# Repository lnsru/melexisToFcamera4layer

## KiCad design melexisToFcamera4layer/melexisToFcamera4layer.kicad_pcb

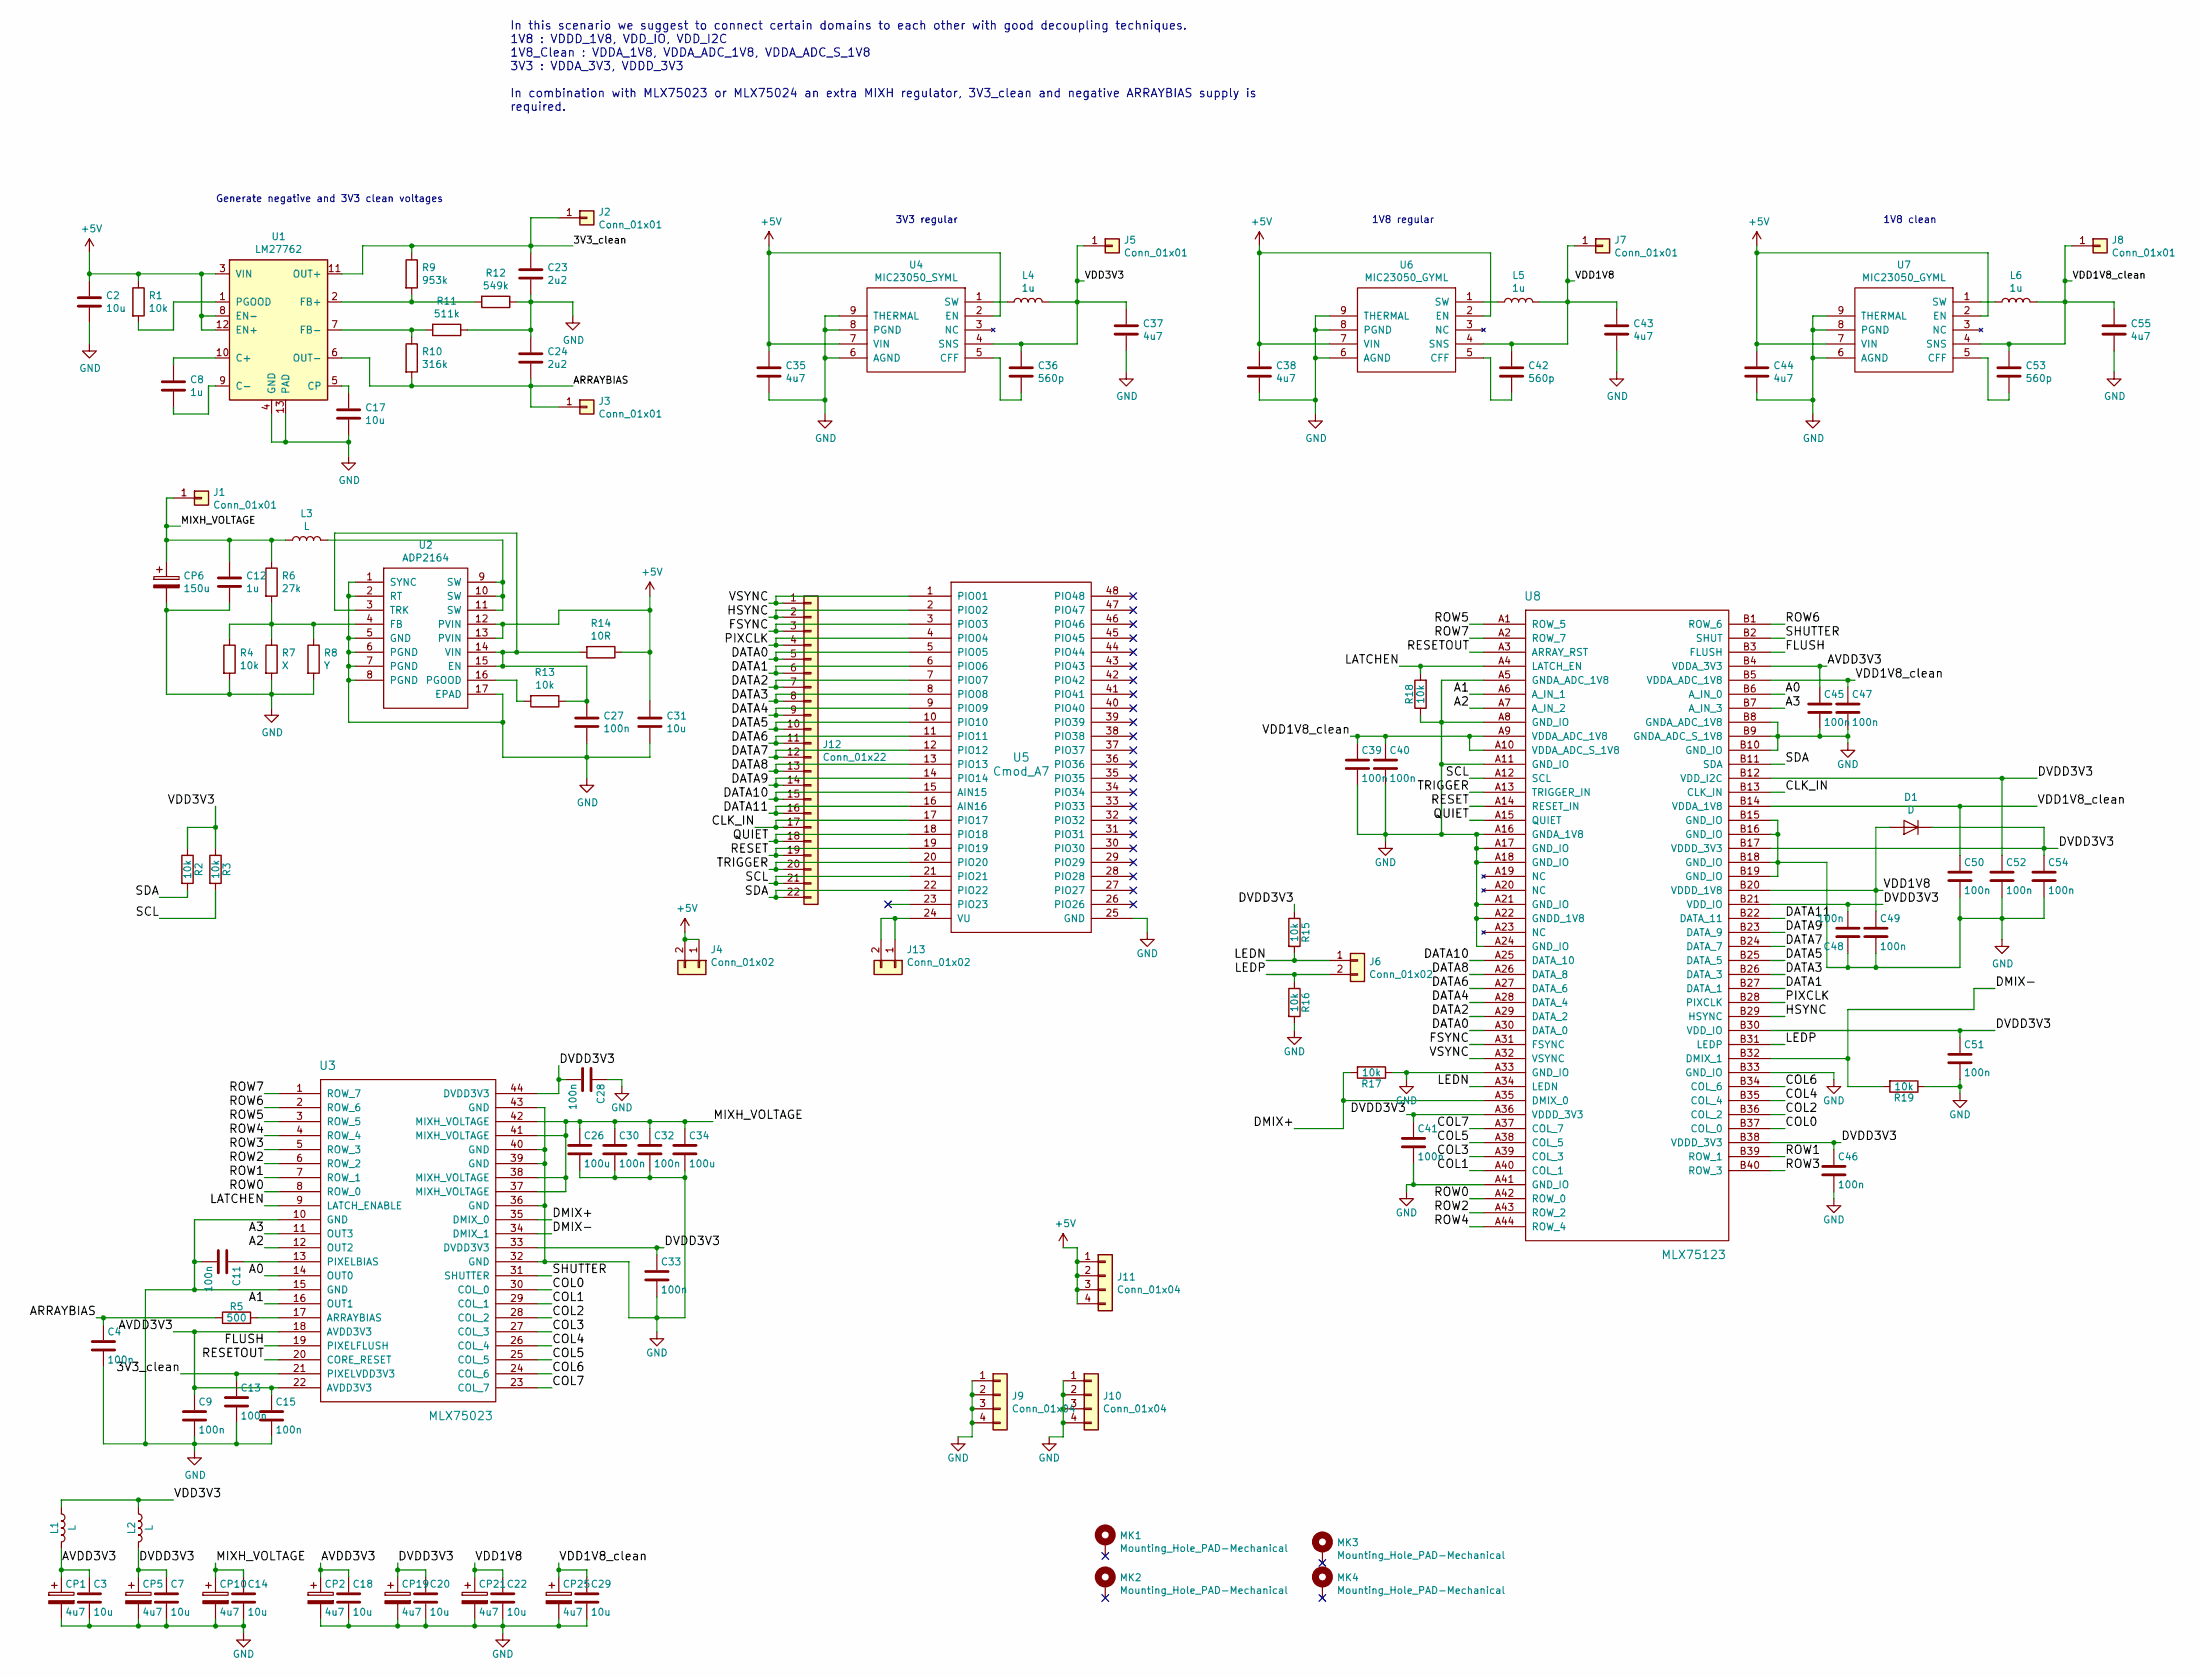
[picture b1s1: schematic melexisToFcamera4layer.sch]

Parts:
C2, C3, C7, C14, C17, C18, C20, C22, C29, C31: 10u; C_0603
C4, C9, C11, C13, C15, C27, C28, C30, C32, C33, C39, C40, C41, C45, C46, C47, C48, C49, C50, C51, C52, C54: 100n; C_0603
C8, C12: 1u; C_0603
C23, C24: 2u2; C_0603
C26, C34: 100u; C_0603
C35, C37, C38, C43, C44, C55: 4u7; C_0603
C36, C42, C53: 560p; C_0603
CP1, CP2, CP5, CP10, CP19, CP21, CP25: 4u7; C_0603
CP6: 150u; C_0603
D1: D; D_0805
J1, J2, J3, J5, J7, J8: Conn_01x01; Measurement_Point_Round-SMD-Pad_Small
J4, J6, J13: Conn_01x02; Pin_Header_Straight_1x02_Pitch2.54mm
J9, J10, J11: Conn_01x04; Pin_Header_Straight_1x04_Pitch2.54mm
J12: Conn_01x22
L1, L2, L3: L; R_1206_HandSoldering
L4, L5, L6: 1u; R_1206_HandSoldering
MK1, MK2, MK3, MK4: Mounting_Hole_PAD-Mechanical; MountingHole_3.2mm_M3_ISO7380
R1, R2, R3, R4, R13, R15, R16, R17, R18, R19: 10k; R_0603
R5: 500; R_0805_HandSoldering
R6: 27k; R_0805_HandSoldering
R7: X; R_0805_HandSoldering
R8: Y; R_0805_HandSoldering
R9: 953k; R_0805_HandSoldering
R10: 316k; R_0805_HandSoldering
R11: 511k; R_0805_HandSoldering
R12: 549k; R_0805_HandSoldering
R14: 10R; R_0805_HandSoldering
U1: LM27762
U2: ADP2164
U3: MLX75023
U4: MIC23050_SYML; MIC23050
U5: Cmod_A7
U6, U7: MIC23050_GYML; MIC23050
U8: MLX75123

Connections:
+5V: C2.1, C31.1, C35.1, C38.1, C44.1, J4.1, J4.2, J11.1, J11.2, J11.3, J11.4, R1.1, R14.1, U1.3 (VIN), U1.8 (EN-), U1.12 (EN+), U2.12 (PVIN), U2.13 (PVIN), U4.2 (EN), U4.7 (VIN), U6.2 (EN), U6.7 (VIN), U7.2 (EN), U7.7 (VIN)
/3V3_clean: C13.1, C23.1, J2.1, R9.1, U1.11 (OUT+), U3.21 (PIXELVDD3V3)
/A0: U3.14 (OUT0), U8.B6 (A_IN_0)
/A1: U3.16 (OUT1), U8.A6 (A_IN_1)
/A2: U3.12 (OUT2), U8.A7 (A_IN_2)
/A3: U3.11 (OUT3), U8.B7 (A_IN_3)
/ARRAYBIAS: C4.1, C24.2, J3.1, R5.1, R10.2, U1.6 (OUT-)
/AVDD3V3: C3.1, C9.1, C15.1, C18.1, C45.1, CP1.1, CP2.1, L1.2, U3.18 (AVDD3V3), U3.22 (AVDD3V3), U8.B4 (VDDA_3V3)
/CLK_IN: J12.17, U5.17 (PIO17), U8.B13 (CLK_IN)
/COL0: U3.30 (COL_0), U8.B37 (COL_0)
/COL1: U3.29 (COL_1), U8.A40 (COL_1)
/COL2: U3.28 (COL_2), U8.B36 (COL_2)
/COL3: U3.27 (COL_3), U8.A39 (COL_3)
/COL4: U3.26 (COL_4), U8.B35 (COL_4)
/COL5: U3.25 (COL_5), U8.A38 (COL_5)
/COL6: U3.24 (COL_6), U8.B34 (COL_6)
/COL7: U3.23 (COL_7), U8.A37 (COL_7)
/DATA0: J12.5, U5.5 (PIO05), U8.A30 (DATA_0)
/DATA1: J12.6, U5.6 (PIO06), U8.B27 (DATA_1)
/DATA2: J12.7, U5.7 (PIO07), U8.A29 (DATA_2)
/DATA3: J12.8, U5.8 (PIO08), U8.B26 (DATA_3)
/DATA4: J12.9, U5.9 (PIO09), U8.A28 (DATA_4)
/DATA5: J12.10, U5.10 (PIO10), U8.B25 (DATA_5)
/DATA6: J12.11, U5.11 (PIO11), U8.A27 (DATA_6)
/DATA7: J12.12, U5.12 (PIO12), U8.B24 (DATA_7)
/DATA8: J12.13, U5.13 (PIO13), U8.A26 (DATA_8)
/DATA9: J12.14, U5.14 (PIO14), U8.B23 (DATA_9)
/DATA10: J12.15, U5.15 (AIN15), U8.A25 (DATA_10)
/DATA11: J12.16, U5.16 (AIN16), U8.B22 (DATA_11)
/DMIX+: R17.2, U3.35 (DMIX_0), U8.A35 (DMIX_0)
/DMIX-: R19.2, U3.34 (DMIX_1), U8.B32 (DMIX_1)
/DVDD3V3: C7.1, C20.1, C28.2, C33.1, C41.1, C46.1, C48.2, C51.1, C52.1, C54.1, CP5.1, CP19.1, D1.1 (K), L2.2, R15.1, U3.33 (DVDD3V3), U3.44 (DVDD3V3), U8.A36 (VDDD_3V3), U8.B12 (VDD_I2C), U8.B17 (VDDD_3V3), U8.B21 (VDD_IO), U8.B30 (VDD_IO), U8.B38 (VDDD_3V3)
/FLUSH: U3.19 (PIXELFLUSH), U8.B3 (FLUSH)
/FSYNC: J12.3, U5.3 (PIO03), U8.A31 (FSYNC)
/HSYNC: J12.2, U5.2 (PIO02), U8.B29 (HSYNC)
/LATCHEN: R18.2, U3.9 (LATCH_ENABLE), U8.A4 (LATCH_EN)
/LEDN: J6.1, R15.2, U8.A34 (LEDN)
/LEDP: J6.2, R16.1, U8.B31 (LEDP)
/MIXH_VOLTAGE: C12.1, C14.1, C26.1, C30.1, C32.1, C34.1, CP6.1, CP10.1, J1.1, L3.1, R6.1, U3.37 (MIXH_VOLTAGE), U3.38 (MIXH_VOLTAGE), U3.41 (MIXH_VOLTAGE), U3.42 (MIXH_VOLTAGE)
/PIXCLK: J12.4, U5.4 (PIO04), U8.B28 (PIXCLK)
/QUIET: J12.18, U5.18 (PIO18), U8.A15 (QUIET)
/RESET: J12.19, U5.19 (PIO19), U8.A14 (RESET_IN)
/RESETOUT: U3.20 (CORE_RESET), U8.A3 (ARRAY_RST)
/ROW0: U3.8 (ROW_0), U8.A42 (ROW_0)
/ROW1: U3.7 (ROW_1), U8.B39 (ROW_1)
/ROW2: U3.6 (ROW_2), U8.A43 (ROW_2)
/ROW3: U3.5 (ROW_3), U8.B40 (ROW_3)
/ROW4: U3.4 (ROW_4), U8.A44 (ROW_4)
/ROW5: U3.3 (ROW_5), U8.A1 (ROW_5)
/ROW6: U3.2 (ROW_6), U8.B1 (ROW_6)
/ROW7: U3.1 (ROW_7), U8.A2 (ROW_7)
/SCL: J12.21, R3.2, U5.21 (PIO21), U8.A12 (SCL)
/SDA: J12.22, R2.2, U5.22 (PIO22), U8.B11 (SDA)
/SHUTTER: U3.31 (SHUTTER), U8.B2 (SHUT)
/TRIGGER: J12.20, U5.20 (PIO20), U8.A13 (TRIGGER_IN)
/VDD1V8: C22.1, C42.1, C43.1, C49.1, CP21.1, D1.2 (A), J7.1, L5.2, U6.4 (SNS), U8.B20 (VDDD_1V8)
/VDD1V8_clean: C29.1, C39.1, C40.1, C47.1, C50.1, C53.1, C55.1, CP25.1, J8.1, L6.2, U7.4 (SNS), U8.A9 (VDDA_ADC_1V8), U8.A10 (VDDA_ADC_S_1V8), U8.B5 (VDDA_ADC_1V8), U8.B14 (VDDA_1V8)
/VDD3V3: C36.1, C37.1, J5.1, L1.1, L2.1, L4.2, R2.1, R3.1, U4.4 (SNS)
/VSYNC: J12.1, U5.1 (PIO01), U8.A32 (VSYNC)
GND: C2.2, C3.2, C4.2, C7.2, C9.2, C11.2, C12.2, C13.2, C14.2, C15.2, C17.2, C18.2, C20.2, C22.2, C23.2, C24.1, C26.2, C27.2, C28.1, C29.2, C30.2, C31.2, C32.2, C33.2, C34.2, C35.2, C37.2, C38.2, C39.2, C40.2, C41.2, C43.2, C44.2, C45.2, C46.2, C47.2, C48.1, C49.2, C50.2, C51.2, C52.2, C54.2, C55.2, CP1.2, CP2.2, CP5.2, CP6.2, CP10.2, CP19.2, CP21.2, CP25.2, J9.1, J9.2, J9.3, J9.4, J10.1, J10.2, J10.3, J10.4, R4.2, R7.2, R8.2, R11.1, R12.1, R16.2, R17.1, R18.1, R19.1, U1.4 (GND), U1.13 (PAD), U2.1 (SYNC), U2.2 (RT), U2.5 (GND), U2.6 (PGND), U2.7 (PGND), U2.8 (PGND), U2.17 (EPAD), U3.10 (GND), U3.15 (GND), U3.32 (GND), U3.36 (GND), U3.39 (GND), U3.40 (GND), U3.43 (GND), U4.6 (AGND), U4.8 (PGND), U4.9 (THERMAL), U5.25 (GND), U6.6 (AGND), U6.8 (PGND), U6.9 (THERMAL), U7.6 (AGND), U7.8 (PGND), U7.9 (THERMAL), U8.A5 (GNDA_ADC_1V8), U8.A8 (GND_IO), U8.A11 (GND_IO), U8.A16 (GNDA_1V8), U8.A17 (GND_IO), U8.A18 (GND_IO), U8.A21 (GND_IO), U8.A22 (GNDD_1V8), U8.A24 (GND_IO), U8.A33 (GND_IO), U8.A41 (GND_IO), U8.B8 (GNDA_ADC_1V8), U8.B9 (GNDA_ADC_S_1V8), U8.B10 (GND_IO), U8.B15 (GND_IO), U8.B16 (GND_IO), U8.B18 (GND_IO), U8.B19 (GND_IO), U8.B33 (GND_IO)
unnamed: C8.1, U1.10 (C+)
unnamed: C8.2, U1.9 (C-)
unnamed: C11.1, U3.13 (PIXELBIAS)
unnamed: C17.1, U1.5 (CP)
unnamed: C27.1, R13.1, R14.2, U2.3 (TRK), U2.14 (VIN), U2.15 (EN)
unnamed: C36.2, U4.5 (CFF)
unnamed: C42.2, U6.5 (CFF)
unnamed: C53.2, U7.5 (CFF)
unnamed: J13.1, J13.2, U5.24 (VU)
unnamed: L3.2, U2.9 (SW), U2.10 (SW), U2.11 (SW)
unnamed: L4.1, U4.1 (SW)
unnamed: L5.1, U6.1 (SW)
unnamed: L6.1, U7.1 (SW)
unnamed: R1.2, U1.1 (PGOOD)
unnamed: R4.1, R6.2, R7.1, R8.1, U2.4 (FB)
unnamed: R5.2, U3.17 (ARRAYBIAS)
unnamed: R10.1, R11.2, U1.7 (FB-)
unnamed: R9.2, R12.2, U1.2 (FB+)
unnamed: R13.2, U2.16 (PGOOD)

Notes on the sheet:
3V3 regular
1V8 regular
1V8 clean
Generate negative and 3V3 clean voltages
In this scenario we suggest to connect certain domains to each other with good decoupling techniques. 1V8 : VDDD_1V8, VDD_IO, VDD_I2C 1V8_Clean : VDDA_1V8, VDDA_ADC_1V8, VDDA_ADC_S_1V8 3V3 : VDDA_3V3, VDDD_3V3 In combination with MLX75023 or MLX75024 an extra MIXH regulator, 3V3_clean and negative 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

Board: 4 copper layers, 106 parts (0 on the bottom side), 79 nets, no tracks yet.

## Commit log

2019-04-07 New project from 1593K Enclosure Template
2019-04-07 Voltage sources added
2019-04-07 Added schematics for all power rails
2019-04-07 Imported Melexis parts. Next step - verify their connections
2019-04-07 Test commit, changed credentials
2019-04-08 Added couple datasheets
2019-04-09 Added component values in the schematic of sensor board
2019-04-09 Assigned footprints to the components on sensor board's schematic
2019-04-09 Added and assigned footprints to sensor board. One still missing :-(
2019-04-10 Finalized adding footprints for sensor board, starting routing it.
2019-04-10 Fixed some weird bug in MLX75123 footprint, started routing
2019-04-11 Started placing components on the sensor board
2019-04-13 Components on sensor board placed together
2019-04-13 Improved schematics, prepared layout for routing
2019-04-14 Sadly freerouting autorouter was not useful for this design
2019-06-07 Create license
    MIT license choosen
